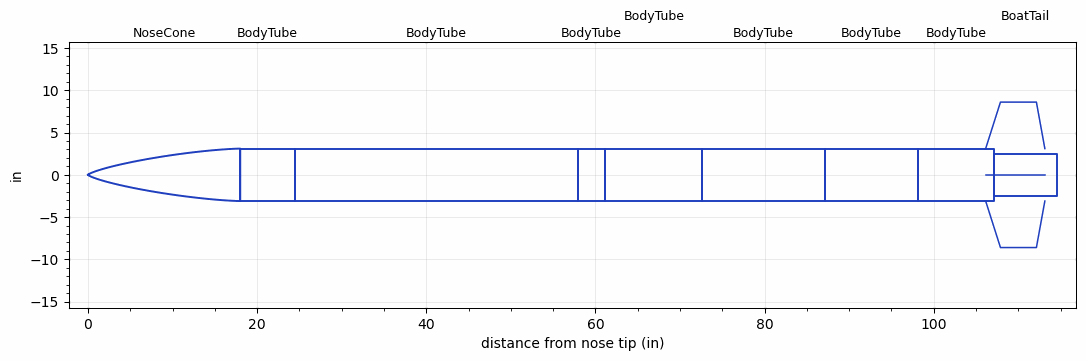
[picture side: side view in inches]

<RASAeroDocument>
 <FileVersion>2</FileVersion>
 <RocketDesign>
  <NoseCone>
   <Length>18</Length>
   <Diameter>6.2</Diameter>
   <Shape>Von Karman Ogive</Shape>
   <Location>0</Location>
  </NoseCone>
  <BodyTube>
   <Length>6.5</Length>
   <Diameter>6.2</Diameter>
   <Location>18</Location>
  </BodyTube>
  <BodyTube>
   <Length>33.3999</Length>
   <Diameter>6.2</Diameter>
   <Location>24.5</Location>
  </BodyTube>
  <BodyTube>
   <Length>3.25</Length>
   <Diameter>6.2</Diameter>
   <Location>57.8999</Location>
  </BodyTube>
  <BodyTube>
   <Length>11.5</Length>
   <Diameter>6.2</Diameter>
   <Location>61.1499</Location>
  </BodyTube>
  <BodyTube>
   <Length>14.5</Length>
   <Diameter>6.2</Diameter>
   <RailGuideDiameter>0.621</RailGuideDiameter>
   <RailGuideHeight>0.684</RailGuideHeight>
   <Location>72.6499</Location>
  </BodyTube>
  <BodyTube>
   <Length>11</Length>
   <Diameter>6.2</Diameter>
   <RailGuideDiameter>0.621</RailGuideDiameter>
   <RailGuideHeight>0.684</RailGuideHeight>
   <Location>87.1498</Location>
  </BodyTube>
  <BodyTube>
   <Length>9</Length>
   <Diameter>6.2</Diameter>
   <Location>98.1498</Location>
   <Fin>
    <Count>4</Count>
    <Chord>7</Chord>
    <Span>5.5</Span>
    <SweepDistance>1.75</SweepDistance>
    <TipChord>4.25</TipChord>
    <Thickness>0.1875</Thickness>
    <Location>1</Location>
    <AirfoilSection>Rounded</AirfoilSection>
   </Fin>
  </BodyTube>
  <BoatTail>
   <Length>7.41</Length>
   <Diameter>5</Diameter>
   <RearDiameter>5</RearDiameter>
   <Location>107.1498</Location>
  </BoatTail>
  <Surface>Sheet Metal</Surface>
  <CD>0</CD>
  <ModifiedBarrowman>False</ModifiedBarrowman>
  <Turbulence>False</Turbulence>
  <UseBooster1>False</UseBooster1>
  <UseBooster2>False</UseBooster2>
 </RocketDesign>
 <LaunchSite>
  <Altitude>2871.0001</Altitude>
  <Pressure>28.9938</Pressure>
  <RodAngle>6</RodAngle>
  <RodLength>154.9997</RodLength>
  <Temperature>86</Temperature>
  <WindSpeed>1.5882</WindSpeed>
 </LaunchSite>
 <Recovery>
  <Altitude1>1476</Altitude1>
  <Altitude2>656.168</Altitude2>
  <DeviceType1>Parachute</DeviceType1>
  <DeviceType2>Parachute</DeviceType2>
  <Event1>True</Event1>
  <Event2>True</Event2>
  <Size1>95.9998</Size1>
  <Size2>35.9999</Size2>
  <EventType1>Altitude</EventType1>
  <EventType2>Apogee</EventType2>
  <CD1>1.35</CD1>
  <CD2>0</CD2>
 </Recovery>
 <SimulationList>
  <Simulation>
   <SustainerLaunchWt>68.2577</SustainerLaunchWt>
   <SustainerCG>67.4295</SustainerCG>
   <SustainerIgnitionDelay>0</SustainerIgnitionDelay>
   <Booster1SeparationDelay>0</Booster1SeparationDelay>
   <Booster1IgnitionDelay>0</Booster1IgnitionDelay>
   <IncludeBooster1>False</IncludeBooster1>
   <Booster2Delay>0</Booster2Delay>
   <IncludeBooster2>False</IncludeBooster2>
  </Simulation>
 </SimulationList>
</RASAeroDocument>
